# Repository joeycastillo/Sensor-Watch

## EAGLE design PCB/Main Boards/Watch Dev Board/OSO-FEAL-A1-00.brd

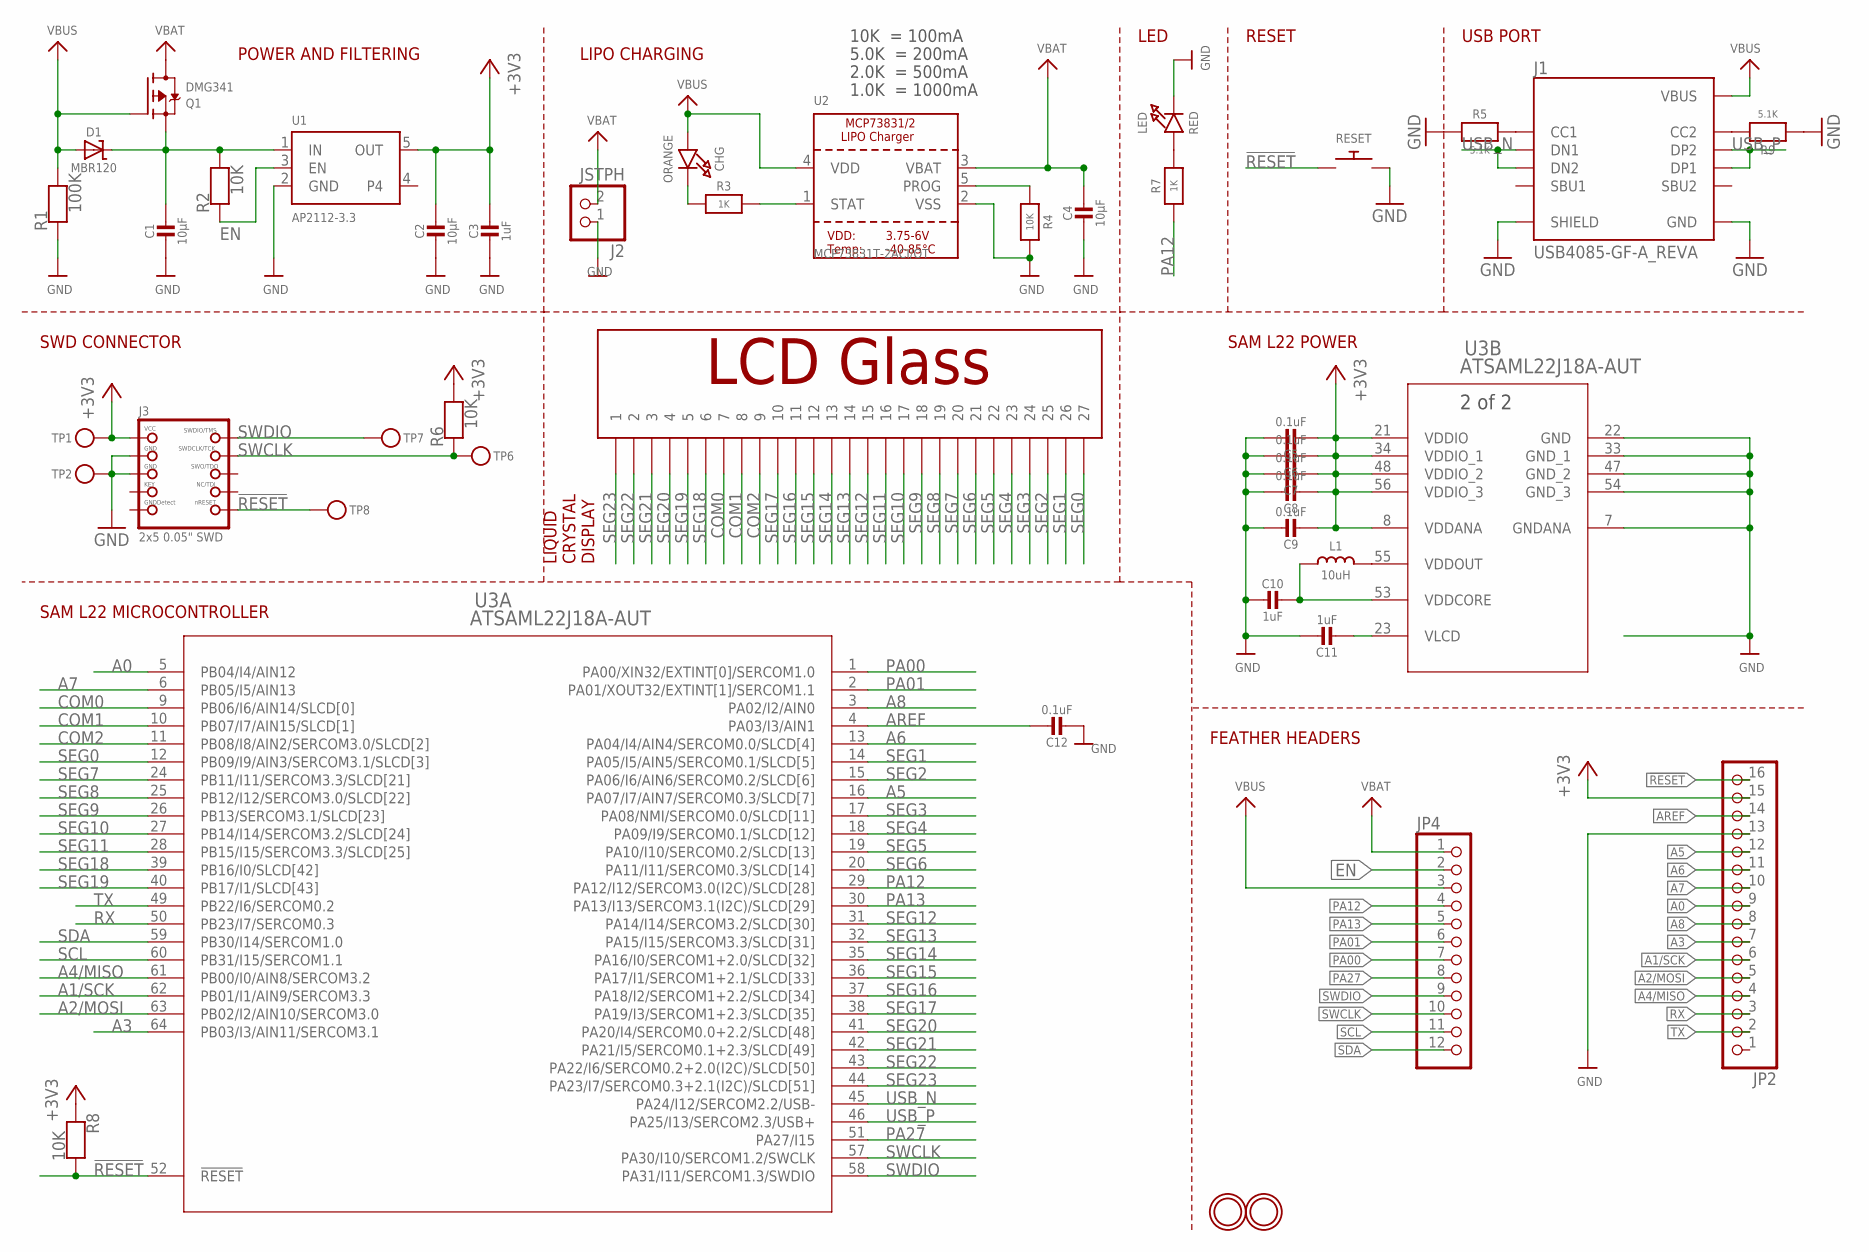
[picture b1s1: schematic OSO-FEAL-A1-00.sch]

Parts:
C1, C2, C4: 10µF; _1206
C3, C10, C11: 1uF; _1206
C5, C6, C7, C8, C9, C12: 0.1uF; 0603-NO
CHG: ORANGE; CHIPLED_0805_NOOUTLINE
D1: MBR120; SOD-123
J1: USB4085-GF-A_REVA; GCT_USB4085-GF-A_REVA
J2: JSTPH; JSTPH2
J3: 2x5 0.05" SWD; 2X05_1.27MM_BOX_NOPOSTS
JP2: HEADER-1X16_MIN; 1X16_ROUND_MIN
JP4: HEADER-1X12_MIN; 1X12_ROUND_MIN
L1: 10uH; MICROBUILDER__0805MP
LED: RED; CHIPLED_0805_NOOUTLINE
Q1: DMG341; SOT23-R
R1: 100K; 0603-NO
R2, R4, R6, R8: 10K; 0603-NO
R3, R7: 1K; 0603-NO
R5, R9: 5.1K; 0603-NO
RESET: SWITCH_PUSHBUTTON_3.5X6MM; TACTILE_3X6MM
TP1, TP2, TP6, TP7, TP8: TESTPOINTROUND2MMNO; TESTPOINT_ROUND_2MM_NO
U1: AP2112-3.3; SOT23-5
U2: MCP73831T-2ACI/OT; SOT23-5
U3: ATSAML22J18A-AUT; TQFP64_10X10MC_MCH-L
U$4: LCD_FEATHER_DISPLAY
U$31, U$32: MOUNTINGHOLE2.5; MOUNTINGHOLE_2.5_PLATED

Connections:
!RESET: J3.10 (NRESET), JP2.16, R8.2, RESET.P$1, TP8.P$1, U3.52 (!RESET)
+3V3: C2.1, C3.1, C5.2, C6.2, C7.2, C8.2, C9.2, J3.1 (VCC), JP2.15, R6.2, R8.1, TP1.P$1, U1.5 (OUT), U3.8 (VDDANA), U3.21 (VDDIO), U3.34 (VDDIO_1), U3.48 (VDDIO_2), U3.56 (VDDIO_3)
A0: JP2.9, U3.5 (PB04/I4/AIN12)
A1/SCK: JP2.6, U3.62 (PB01/I1/AIN9/SERCOM3.3)
A2/MOSI: JP2.5, U3.63 (PB02/I2/AIN10/SERCOM3.0)
A3: JP2.7, U3.64 (PB03/I3/AIN11/SERCOM3.1)
A4/MISO: JP2.4, U3.61 (PB00/I0/AIN8/SERCOM3.2)
A5: JP2.12, U3.16 (PA07/I7/AIN7/SERCOM0.3/SLCD[7])
A6: JP2.11, U3.13 (PA04/I4/AIN4/SERCOM0.0/SLCD[4])
A7: JP2.10, U3.6 (PB05/I5/AIN13)
A8: JP2.8, U3.3 (PA02/I2/AIN0)
AREF: C12.1, JP2.14, U3.4 (PA03/I3/AIN1)
CHG: CHG.C, R3.1
COM0: U3.9 (PB06/I6/AIN14/SLCD[0]), U$4.P$7 (7)
COM1: U3.10 (PB07/I7/AIN15/SLCD[1]), U$4.P$8 (8)
COM2: U3.11 (PB08/I8/AIN2/SERCOM3.0/SLCD[2]), U$4.P$9 (9)
EN: JP4.2, R2.1, U1.3 (EN)
GND: C1.2, C2.2, C3.2, C4.2, C5.1, C6.1, C7.1, C8.1, C9.1, C10.2, C11.1, C12.2, J1.A1 (GND), J1.A12 (GND), J1.B1 (GND), J1.B12 (GND), J1.P1 (SHIELD), J1.P2 (SHIELD), J1.P3 (SHIELD), J1.P4 (SHIELD), J2.1, J3.3 (GND), J3.5 (GND), JP2.13, LED.C, R1.1, R4.2, R5.1, R9.2, RESET.P$2, TP2.P$1, U1.2 (GND), U2.2 (VSS), U3.7 (GNDANA), U3.22 (GND), U3.33 (GND_1), U3.47 (GND_2), U3.54 (GND_3)
unnamed: LED.A, R7.2
unnamed: J1.A5 (CC1), R5.2
unnamed: J1.B5 (CC2), R9.1
PA00: JP4.7, U3.1 (PA00/XIN32/EXTINT[0]/SERCOM1.0)
PA01: JP4.6, U3.2 (PA01/XOUT32/EXTINT[1]/SERCOM1.1)
PA12: JP4.4, R7.1, U3.29 (PA12/I12/SERCOM3.0(I2C)/SLCD[28])
PA13: JP4.5, U3.30 (PA13/I13/SERCOM3.1(I2C)/SLCD[29])
PA27: JP4.8, U3.51 (PA27/I15)
PROG: R4.1, U2.5 (PROG)
RX: JP2.3, U3.50 (PB23/I7/SERCOM0.3)
SCL: JP4.11, U3.60 (PB31/I15/SERCOM1.1)
SDA: JP4.12, U3.59 (PB30/I14/SERCOM1.0)
SEG0: U3.12 (PB09/I9/AIN3/SERCOM3.1/SLCD[3]), U$4.P$27 (27)
SEG1: U3.14 (PA05/I5/AIN5/SERCOM0.1/SLCD[5]), U$4.P$26 (26)
SEG2: U3.15 (PA06/I6/AIN6/SERCOM0.2/SLCD[6]), U$4.P$25 (25)
SEG3: U3.17 (PA08/NMI/SERCOM0.0/SLCD[11]), U$4.P$24 (24)
SEG4: U3.18 (PA09/I9/SERCOM0.1/SLCD[12]), U$4.P$23 (23)
SEG5: U3.19 (PA10/I10/SERCOM0.2/SLCD[13]), U$4.P$22 (22)
SEG6: U3.20 (PA11/I11/SERCOM0.3/SLCD[14]), U$4.P$21 (21)
SEG7: U3.24 (PB11/I11/SERCOM3.3/SLCD[21]), U$4.P$20 (20)
SEG8: U3.25 (PB12/I12/SERCOM3.0/SLCD[22]), U$4.P$19 (19)
SEG9: U3.26 (PB13/SERCOM3.1/SLCD[23]), U$4.P$18 (18)
SEG10: U3.27 (PB14/I14/SERCOM3.2/SLCD[24]), U$4.P$17 (17)
SEG11: U3.28 (PB15/I15/SERCOM3.3/SLCD[25]), U$4.P$16 (16)
SEG12: U3.31 (PA14/I14/SERCOM3.2/SLCD[30]), U$4.P$15 (15)
SEG13: U3.32 (PA15/I15/SERCOM3.3/SLCD[31]), U$4.P$14 (14)
SEG14: U3.35 (PA16/I0/SERCOM1+2.0/SLCD[32]), U$4.P$13 (13)
SEG15: U3.36 (PA17/I1/SERCOM1+2.1/SLCD[33]), U$4.P$12 (12)
SEG16: U3.37 (PA18/I2/SERCOM1+2.2/SLCD[34]), U$4.P$11 (11)
SEG17: U3.38 (PA19/I3/SERCOM1+2.3/SLCD[35]), U$4.P$10 (10)
SEG18: U3.39 (PB16/I0/SLCD[42]), U$4.P$6 (6)
SEG19: U3.40 (PB17/I1/SLCD[43]), U$4.P$5 (5)
SEG20: U3.41 (PA20/I4/SERCOM0.0+2.2/SLCD[48]), U$4.P$4 (4)
SEG21: U3.42 (PA21/I5/SERCOM0.1+2.3/SLCD[49]), U$4.P$3 (3)
SEG22: U3.43 (PA22/I6/SERCOM0.2+2.0(I2C)/SLCD[50]), U$4.P$2 (2)
SEG23: U3.44 (PA23/I7/SERCOM0.3+2.1(I2C)/SLCD[51]), U$4.P$1 (1)
STAT: R3.2, U2.1 (STAT)
SWCLK: J3.4 (SWDCLK), JP4.10, R6.1, TP6.P$1, U3.57 (PA30/I10/SERCOM1.2/SWCLK)
SWDIO: J3.2 (SWDIO), JP4.9, TP7.P$1, U3.58 (PA31/I11/SERCOM1.3/SWDIO)
TX: JP2.2, U3.49 (PB22/I6/SERCOM0.2)
USB_N: J1.A7 (DN1), J1.B7 (DN2), U3.45 (PA24/I12/SERCOM2.2/USB-)
USB_P: J1.A6 (DP1), J1.B6 (DP2), U3.46 (PA25/I13/SERCOM2.3/USB+)
VBAT: C4.1, J2.2, JP4.1, Q1.3 (D), U2.3 (VBAT)
VBUS: CHG.A, D1.A, J1.A4 (VBUS), J1.A9 (VBUS), J1.B4 (VBUS), J1.B9 (VBUS), JP4.3, Q1.1 (G), R1.2, U2.4 (VDD)
VDDCORE: C10.1, L1.1, U3.53 (VDDCORE)
VDDOUT: L1.2, U3.55 (VDDOUT)
VHI: C1.1, D1.C, Q1.2 (S), R2.2, U1.1 (IN)
VLCD: C11.2, U3.23 (VLCD)

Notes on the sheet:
LIPO CHARGING
LED
RESET
POWER AND FILTERING
10K = 100mA
5.0K = 200mA
2.0K = 500mA
1.0K = 1000mA
FEATHER HEADERS
USB PORT
SAM L22 POWER
SAM L22 MICROCONTROLLER
SWD CONNECTOR
LIQUID CRYSTAL DISPLAY

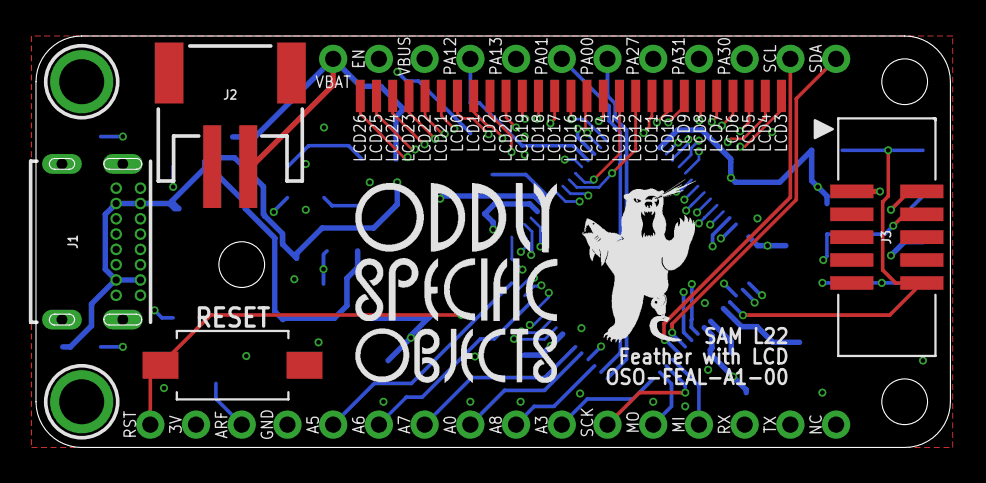
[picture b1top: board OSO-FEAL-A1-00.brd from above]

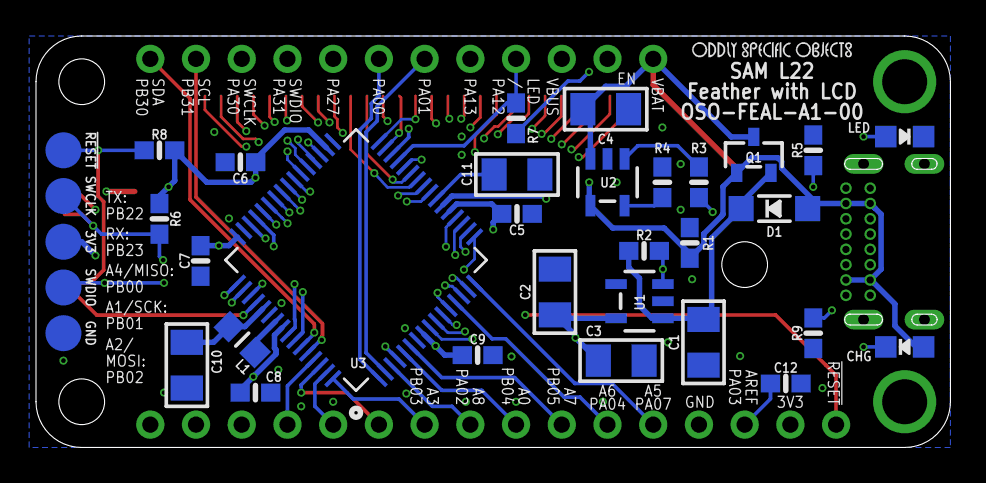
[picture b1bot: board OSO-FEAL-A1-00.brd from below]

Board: 4 copper layers, 50.8 x 22.9 mm, 46 parts (35 on the bottom side), 66 nets.

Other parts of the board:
U$6: OSO_WORDMARK_THREELINE_450MIL_1000DPI
U$9: OSO_BEAR_250X360MIL_1000DPI
U$12: OSO_WORDMARK_ONELINE_350MIL_1000DPI

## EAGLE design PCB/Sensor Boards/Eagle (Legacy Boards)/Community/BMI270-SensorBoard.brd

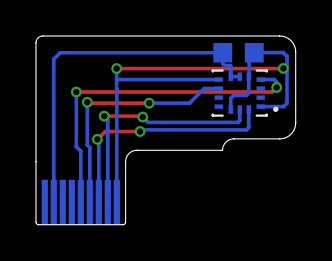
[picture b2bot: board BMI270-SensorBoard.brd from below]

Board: 2 copper layers, 14.4 x 10.5 mm, 3 parts (2 on the bottom side), 6 nets.

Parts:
C1: C0603K
U$1: BMI270; XDCR_BMI270
U$3: FH19C-9S-0.5SH_10-FFC; FH19C9S05SH10-FFC

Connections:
GND: C1.2, U$1.6, U$1.7, U$3.2
INT1: U$1.4, U$3.5
INT2: U$1.9, U$3.6
PWR: C1.1, U$1.1, U$1.5, U$1.8, U$1.12, U$3.9
SCL: U$1.13, U$3.8
SDA: U$1.14, U$3.7

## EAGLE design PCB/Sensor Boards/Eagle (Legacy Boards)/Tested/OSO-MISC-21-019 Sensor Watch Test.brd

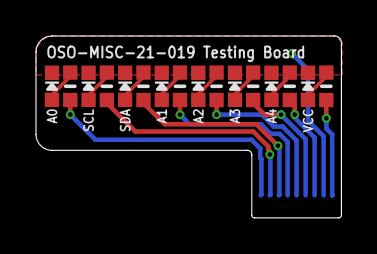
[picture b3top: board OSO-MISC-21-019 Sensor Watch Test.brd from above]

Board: 2 copper layers, 17.0 x 10.1 mm, 17 parts (0 on the bottom side), 17 nets.

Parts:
A0, A1, A2, A3, A4: RED; CHIPLED_0603_NOOUTLINE
R1, R2, R3, R4, R5, R6, R7, R8: 1K; _0603MP
SCL: RED; CHIPLED_0603_NOOUTLINE
SDA: RED; CHIPLED_0603_NOOUTLINE
U$3: FH19C-9S-0.5SH_10-FFC; FH19C9S05SH10-FFC
VCC: RED; CHIPLED_0603_NOOUTLINE

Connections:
A0: R6.1, U$3.9
A1_SCK: R3.1, U$3.6
A2_MOSI: R2.1, U$3.5
A3_CS: R1.1, U$3.4
A4_MISO: R7.1, U$3.3
GND: A0.C, A1.C, A2.C, A3.C, A4.C, SCL.C, SDA.C, U$3.2, VCC.C
unnamed: A4.A, R7.2
unnamed: A3.A, R1.2
unnamed: A2.A, R2.2
unnamed: A1.A, R3.2
unnamed: R4.2, SDA.A
unnamed: R5.2, SCL.A
unnamed: A0.A, R6.2
unnamed: R8.2, VCC.A
SCL: R5.1, U$3.8
SDA: R4.1, U$3.7
VCC: R8.1, U$3.1

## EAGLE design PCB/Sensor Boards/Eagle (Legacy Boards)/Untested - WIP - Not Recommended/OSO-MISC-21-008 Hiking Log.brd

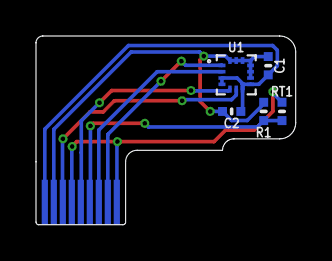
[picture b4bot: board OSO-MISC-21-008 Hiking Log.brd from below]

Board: 2 copper layers, 14.4 x 10.5 mm, 6 parts (5 on the bottom side), 8 nets.

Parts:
C1: 10µF; _0402MP
C2: 0.1uF; _0402MP
R1: 1% 10K; _0402MP
RT1: NTC 10K; _0402MP
U1: LIS2DHTR; PQFN35P200X200X100-14N
U$3: FH19C-9S-0.5SH_10-FFC; FH19C9S05SH10-FFC

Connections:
3.3V: C1.1, C2.2, U1.3, U1.4, U1.7, U1.8, U$3.1
GND: C1.2, C2.1, R1.2, U1.9, U1.10, U1.11, U1.12, U1.13, U1.14, U$3.2
INT1: U1.6, U$3.3
INT2: U1.5, U$3.5
SCL: U1.1, U$3.8
SDA: U1.2, U$3.7
THERM_PWR: RT1.1, U$3.4, U$3.9
TSENSE: R1.1, RT1.2, U$3.6

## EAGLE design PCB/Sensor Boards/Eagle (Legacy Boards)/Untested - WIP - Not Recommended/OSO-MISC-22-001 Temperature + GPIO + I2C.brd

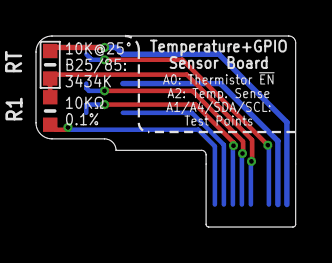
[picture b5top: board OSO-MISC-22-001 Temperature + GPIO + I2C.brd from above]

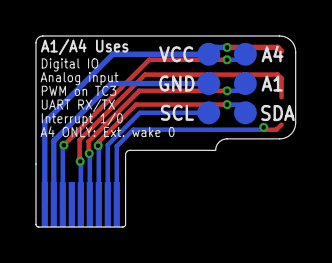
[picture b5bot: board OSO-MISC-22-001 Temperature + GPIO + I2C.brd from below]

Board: 2 copper layers, 14.4 x 10.6 mm, 9 parts (6 on the bottom side), 8 nets.

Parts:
A1, A4: TPB1,27; B1,27
GND: TPB1,27; B1,27
R1: 1% 10K; _0603MP
RT: NTC 10K; _0603MP
SCL: TPB1,27; B1,27
SDA: TPB1,27; B1,27
U$3: FH19C-9S-0.5SH_10-FFC; FH19C9S05SH10-FFC
VCC: TPB1,27; B1,27

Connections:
A0_TEMP_ENABLE: R1.2, U$3.9
A1_SERCOM3.3: A1.TP, U$3.6
A2_TEMP_SENSE: R1.1, RT.2, U$3.5
A4_SERCOM3.2_TC3.0: A4.TP, U$3.3
GND: GND.TP, U$3.2
SCL: SCL.TP, U$3.8
SDA: SDA.TP, U$3.7
VCC: RT.1, U$3.1, VCC.TP

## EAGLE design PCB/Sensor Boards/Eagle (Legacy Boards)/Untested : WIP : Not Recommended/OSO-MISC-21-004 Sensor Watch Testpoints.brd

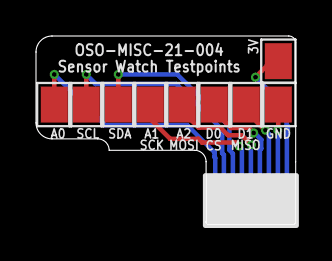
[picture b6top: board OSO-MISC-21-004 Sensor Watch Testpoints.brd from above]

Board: 2 copper layers, 14.4 x 10.5 mm, 10 parts (0 on the bottom side), 9 nets.

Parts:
3V: MICROBUILDER_PAD-1.5X2.0
A0, A1, A2: MICROBUILDER_PAD-1.5X2.0
D0, D1: MICROBUILDER_PAD-1.5X2.0
GND: MICROBUILDER_PAD-1.5X2.0
SCL: MICROBUILDER_PAD-1.5X2.0
SDA: MICROBUILDER_PAD-1.5X2.0
U$3: FH19C-9S-0.5SH_10-FFC; FH19C9S05SH10-FFC

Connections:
A0: A0.P$1, U$3.9
A1/SCK: A1.P$1, U$3.6
A2/MOSI: A2.P$1, U$3.5
D0/CS: D0.P$1, U$3.4
D1/MISO: D1.P$1, U$3.3
GND: GND.P$1, U$3.2
SCL: SCL.P$1, U$3.8
SDA: SDA.P$1, U$3.7
VCC: 3V.P$1, U$3.1

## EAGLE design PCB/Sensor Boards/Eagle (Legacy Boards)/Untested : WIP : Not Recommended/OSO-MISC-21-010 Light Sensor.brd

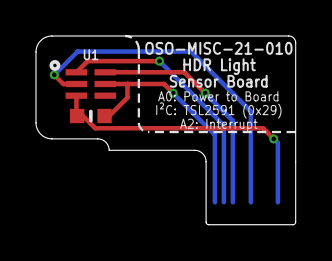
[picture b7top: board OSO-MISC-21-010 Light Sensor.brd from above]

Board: 2 copper layers, 14.4 x 10.5 mm, 3 parts (0 on the bottom side), 5 nets.

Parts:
C1: 1uF; _0603MP
U1: TSL2591; DFN6_TAOS
U$3: FH19C-9S-0.5SH_10-FFC; FH19C9S05SH10-FFC

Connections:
BOARD_POWER: C1.1, U1.5, U$3.9
GND: C1.2, U1.3, U$3.2
INT: U1.2, U$3.5
SCL: U1.1, U$3.8
SDA: U1.6, U$3.7

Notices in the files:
parts and their libraries:
microbuilder: This work is placed in the public domain, and may be freely used for commercial and non-commercial work with the following conditions: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
My Stuff: cc-by-sa 4.0
